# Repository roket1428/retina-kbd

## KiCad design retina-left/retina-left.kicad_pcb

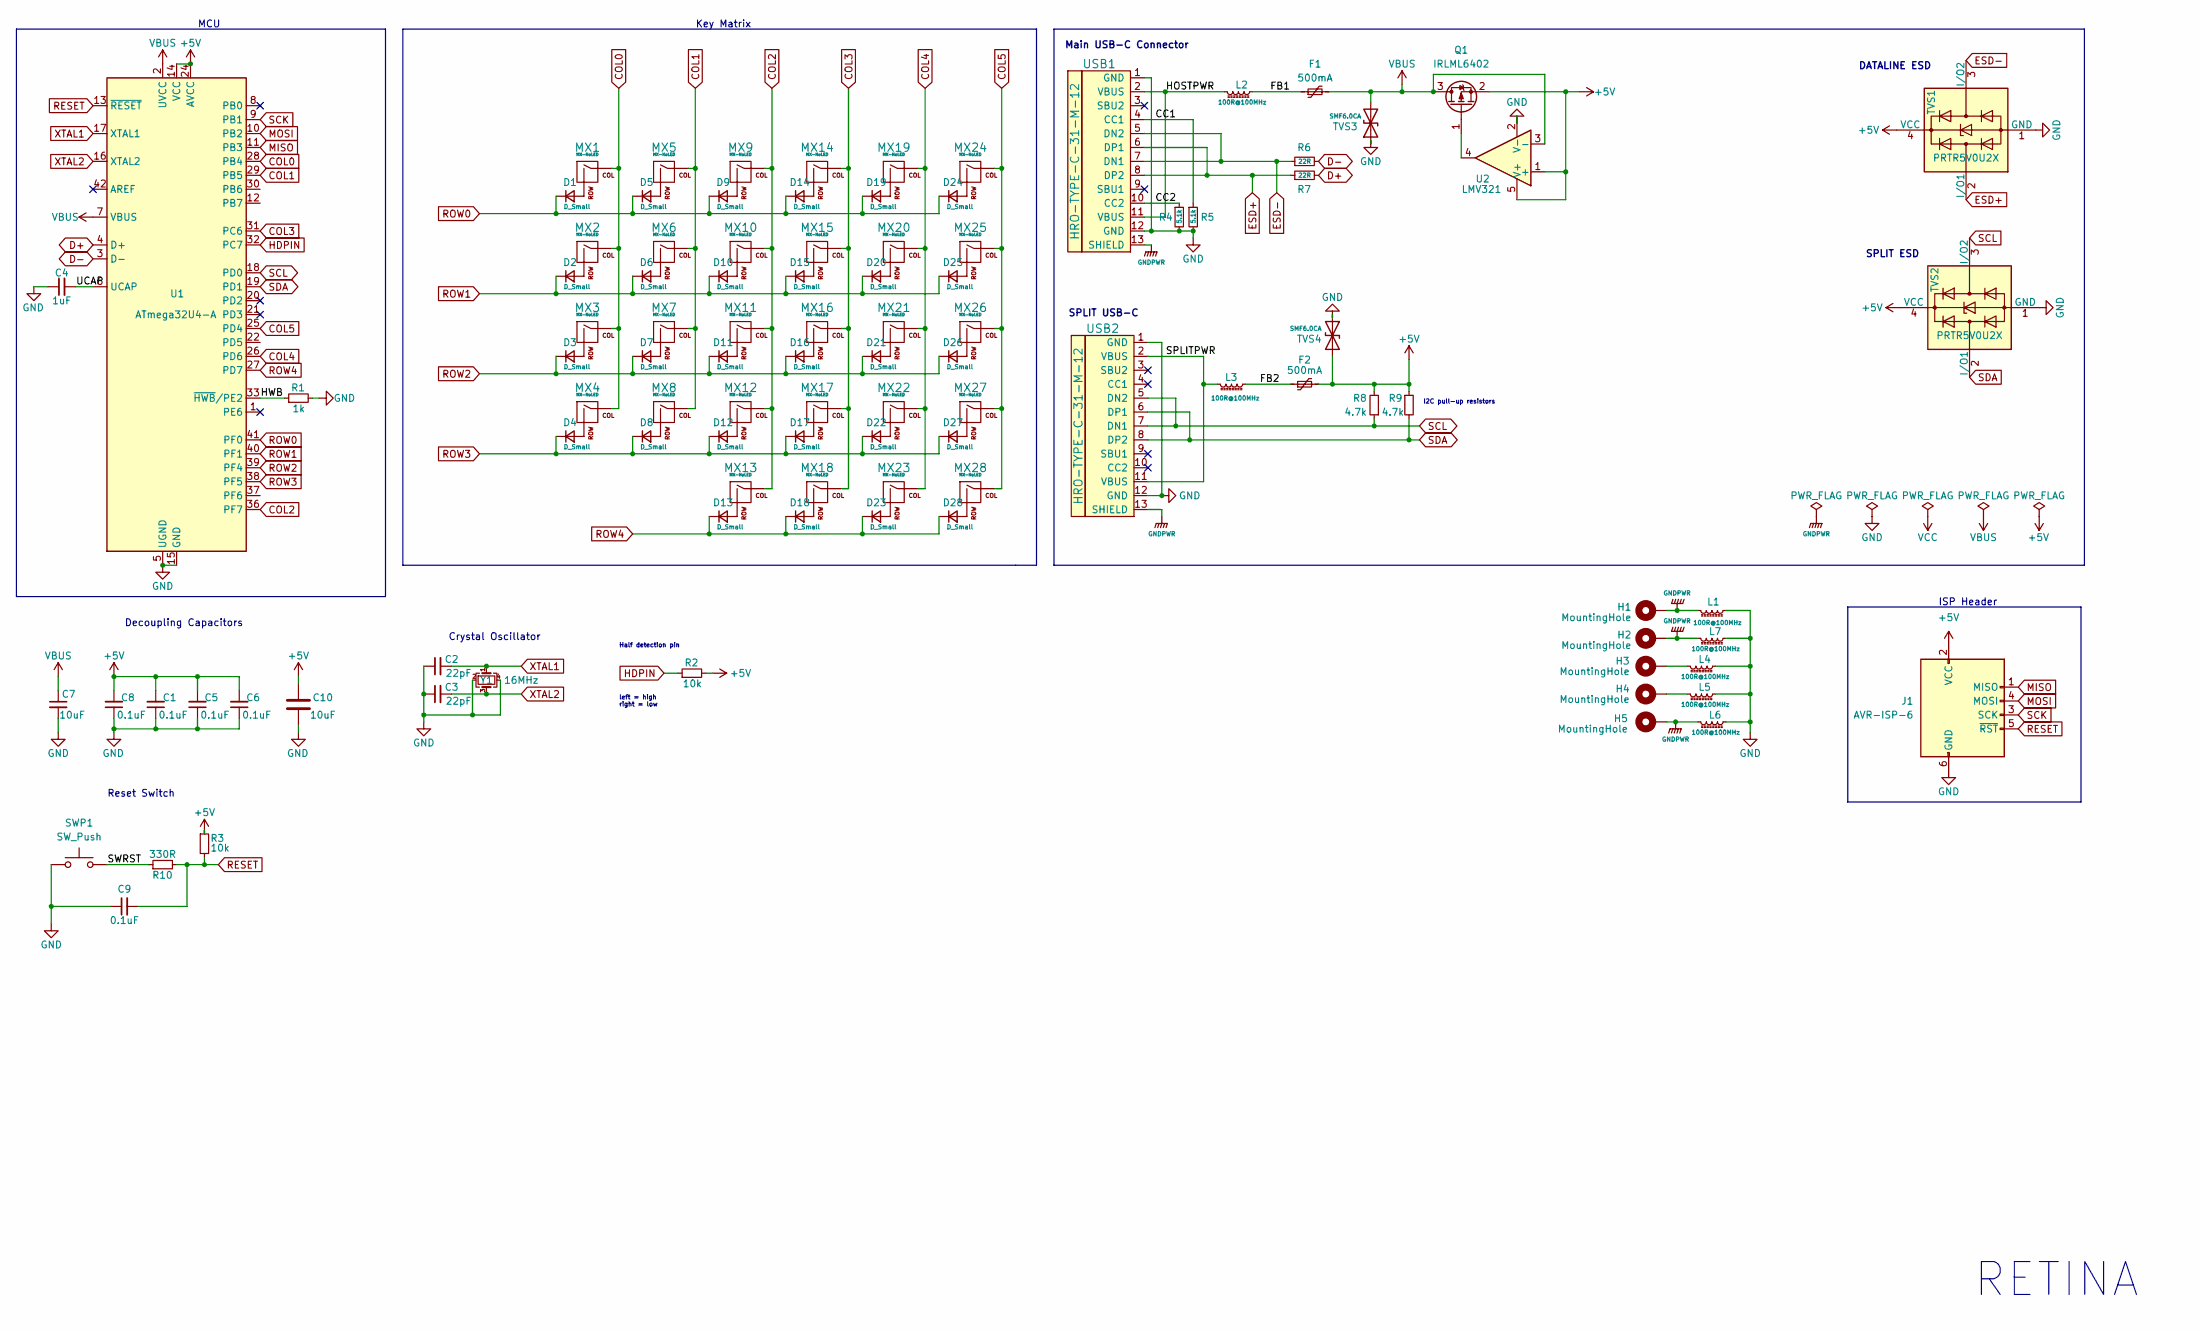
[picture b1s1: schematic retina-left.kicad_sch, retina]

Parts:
C1, C5, C6, C8, C9: 0.1uF; C_0805_2012Metric_Pad1.18x1.45mm_HandSolder
C2, C3: 22pF; C_0805_2012Metric_Pad1.18x1.45mm_HandSolder
C4: 1uF; C_0805_2012Metric_Pad1.18x1.45mm_HandSolder
C7, C10: 10uF; C_0805_2012Metric_Pad1.18x1.45mm_HandSolder
D1, D2, D3, D4, D5, D6, D7, D8, D9, D10, D11, D12, D13, D14, D15, D16, D17, D18, D19, D20, D21, D22, D23, D24, D25, D26, D27, D28: D_Small; D_DO-35_SOD27_P7.62mm
F1, F2: 500mA; Fuse_1206_3216Metric_Pad1.42x1.75mm_HandSolder
H1, H2, H3, H4, H5: MountingHole; MountingHole_2.2mm_M2_Pad_Via
J1: AVR-ISP-6; Conn_AVR_ISP_6
L1, L2, L3, L4, L5, L6, L7: 100R@100MHz; L_0805_2012Metric_Pad1.05x1.20mm_HandSolder
MX1, MX2, MX3, MX4, MX5, MX6, MX7, MX8, MX9, MX10, MX11, MX12, MX13, MX14, MX15, MX16, MX17, MX18, MX19, MX20, MX21, MX22, MX23, MX24, MX25, MX26, MX27, MX28: MX-NoLED; MXOnly-1U-Hotswap
Q1: IRLML6402; SOT-23_Handsoldering
R1: 1k; R_0805_2012Metric_Pad1.20x1.40mm_HandSolder
R2, R3: 10k; R_0805_2012Metric_Pad1.20x1.40mm_HandSolder
R4, R5: 5.1k; R_0805_2012Metric_Pad1.20x1.40mm_HandSolder
R6, R7: 22R; R_0805_2012Metric_Pad1.20x1.40mm_HandSolder
R8, R9: 4.7k; R_0805_2012Metric_Pad1.20x1.40mm_HandSolder
R10: 330R; R_0805_2012Metric_Pad1.20x1.40mm_HandSolder
SWP1: SW_Push; K2-1187SQ-A4SW-06
TVS1, TVS2: PRTR5V0U2X; SOT-143
TVS3, TVS4: SMF6.0CA; D_SOD-123F
U1: ATmega32U4-A; TQFP-44_10x10mm_P0.8mm
U2: LMV321; SOT-23-5_HandSoldering
USB1, USB2: HRO-TYPE-C-31-M-12; HRO-TYPE-C-31-M-12-HandSoldering
Y1: 16MHz; Crystal_SMD_3225-4Pin_3.2x2.5mm_HandSoldering

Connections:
+5V: C1.2, C5.2, C6.2, C8.2, C10.2, F2.2, J1.2 (VCC), Q1.2 (S), R2.2, R3.1, R8.2, R9.1, TVS1.4 (VCC), TVS2.4 (VCC), TVS4.2 (A2), U1.14 (VCC), U1.24 (AVCC), U1.34 (VCC), U1.44 (AVCC), U2.1 (+), U2.5 (V+)
/CC1: R5.1, USB1.4 (CC1)
/CC2: R4.1, USB1.10 (CC2)
/FB1: F1.1, L2.1
/FB2: F2.1, L3.1
/HOSTPWR: L2.2, USB1.2 (VBUS), USB1.11 (VBUS)
/HWB: R1.1, U1.33 (~HWB/PE2)
/SPLITPWR: L3.2, USB2.2 (VBUS), USB2.11 (VBUS)
/SWRST: R10.1, SWP1.2
/UCAP: C4.2, U1.6 (UCAP)
COL0: MX1.1 (COL), MX2.1 (COL), MX3.1 (COL), MX4.1 (COL), U1.28 (PB4)
COL1: MX5.1 (COL), MX6.1 (COL), MX7.1 (COL), MX8.1 (COL), U1.29 (PB5)
COL2: MX9.1 (COL), MX10.1 (COL), MX11.1 (COL), MX12.1 (COL), MX13.1 (COL), U1.36 (PF7)
COL3: MX14.1 (COL), MX15.1 (COL), MX16.1 (COL), MX17.1 (COL), MX18.1 (COL), U1.31 (PC6)
COL4: MX19.1 (COL), MX20.1 (COL), MX21.1 (COL), MX22.1 (COL), MX23.1 (COL), U1.26 (PD6)
COL5: MX24.1 (COL), MX25.1 (COL), MX26.1 (COL), MX27.1 (COL), MX28.1 (COL), U1.25 (PD4)
D+: R7.2, U1.4 (D+)
D-: R6.2, U1.3 (D-)
ESD+: R7.1, TVS1.2 (I/O1), USB1.6 (DP1), USB1.8 (DP2)
ESD-: R6.1, TVS1.3 (I/O2), USB1.5 (DN2), USB1.7 (DN1)
GND: C1.1, C2.1, C3.1, C4.1, C5.1, C6.1, C7.2, C8.1, C9.1, C10.1, J1.6 (GND), L1.1, L4.1, L5.1, L6.1, L7.1, R1.2, R4.2, R5.2, SWP1.1, TVS1.1 (GND), TVS2.1 (GND), TVS3.1 (A1), TVS4.1 (A1), U1.5 (UGND), U1.15 (GND), U1.23 (GND), U1.35 (GND), U1.43 (GND), U2.2 (V-), USB1.1 (GND), USB1.12 (GND), USB2.1 (GND), USB2.12 (GND), Y1.2, Y1.4
GNDPWR: H1.1, H2.1, H5.1, L1.2, L6.2, L7.2, USB1.13 (SHIELD), USB2.13 (SHIELD)
HDPIN: R2.1, U1.32 (PC7)
MISO: J1.1 (MISO), U1.11 (PB3)
MOSI: J1.4 (MOSI), U1.10 (PB2)
unnamed: D1.2 (A), MX1.2 (ROW)
unnamed: D2.2 (A), MX2.2 (ROW)
unnamed: D3.2 (A), MX3.2 (ROW)
unnamed: D4.2 (A), MX4.2 (ROW)
unnamed: D5.2 (A), MX5.2 (ROW)
unnamed: D6.2 (A), MX6.2 (ROW)
unnamed: D7.2 (A), MX7.2 (ROW)
unnamed: D8.2 (A), MX8.2 (ROW)
unnamed: D9.2 (A), MX9.2 (ROW)
unnamed: D10.2 (A), MX10.2 (ROW)
unnamed: D11.2 (A), MX11.2 (ROW)
unnamed: D12.2 (A), MX12.2 (ROW)
unnamed: D13.2 (A), MX13.2 (ROW)
unnamed: D14.2 (A), MX14.2 (ROW)
unnamed: D15.2 (A), MX15.2 (ROW)
unnamed: D16.2 (A), MX16.2 (ROW)
unnamed: D17.2 (A), MX17.2 (ROW)
unnamed: D18.2 (A), MX18.2 (ROW)
unnamed: D19.2 (A), MX19.2 (ROW)
unnamed: D20.2 (A), MX20.2 (ROW)
unnamed: D21.2 (A), MX21.2 (ROW)
unnamed: D22.2 (A), MX22.2 (ROW)
unnamed: D23.2 (A), MX23.2 (ROW)
unnamed: D24.2 (A), MX24.2 (ROW)
unnamed: D25.2 (A), MX25.2 (ROW)
unnamed: D26.2 (A), MX26.2 (ROW)
unnamed: D27.2 (A), MX27.2 (ROW)
unnamed: D28.2 (A), MX28.2 (ROW)
unnamed: H3.1, L4.2
unnamed: H4.1, L5.2
unnamed: Q1.1 (G), U2.4
RESET: C9.2, J1.5 (~RST), R3.2, R10.2, U1.13 (~RESET)
ROW0: D1.1 (K), D5.1 (K), D9.1 (K), D14.1 (K), D19.1 (K), D24.1 (K), U1.41 (PF0)
ROW1: D2.1 (K), D6.1 (K), D10.1 (K), D15.1 (K), D20.1 (K), D25.1 (K), U1.40 (PF1)
ROW2: D3.1 (K), D7.1 (K), D11.1 (K), D16.1 (K), D21.1 (K), D26.1 (K), U1.39 (PF4)
ROW3: D4.1 (K), D8.1 (K), D12.1 (K), D17.1 (K), D22.1 (K), D27.1 (K), U1.38 (PF5)
ROW4: D13.1 (K), D18.1 (K), D23.1 (K), D28.1 (K), U1.27 (PD7)
SCK: J1.3 (SCK), U1.9 (PB1)
SCL: R8.1, TVS2.3 (I/O2), U1.18 (PD0), USB2.5 (DN2), USB2.7 (DN1)
SDA: R9.2, TVS2.2 (I/O1), U1.19 (PD1), USB2.6 (DP1), USB2.8 (DP2)
VBUS: C7.1, F1.2, Q1.3 (D), TVS3.2 (A2), U1.2 (UVCC), U1.7 (VBUS), U2.3 (-)
XTAL1: C2.2, U1.17 (XTAL1), Y1.1
XTAL2: C3.2, U1.16 (XTAL2), Y1.3

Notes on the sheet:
Reset Switch
MCU
SPLIT ESD
DATALINE ESD
Crystal Oscillator
I2C pull-up resistors
left = high right = low
Half detection pin
Main USB-C Connector
SPLIT USB-C
Decoupling Capacitors
ISP Header
Key Matrix
RETINA

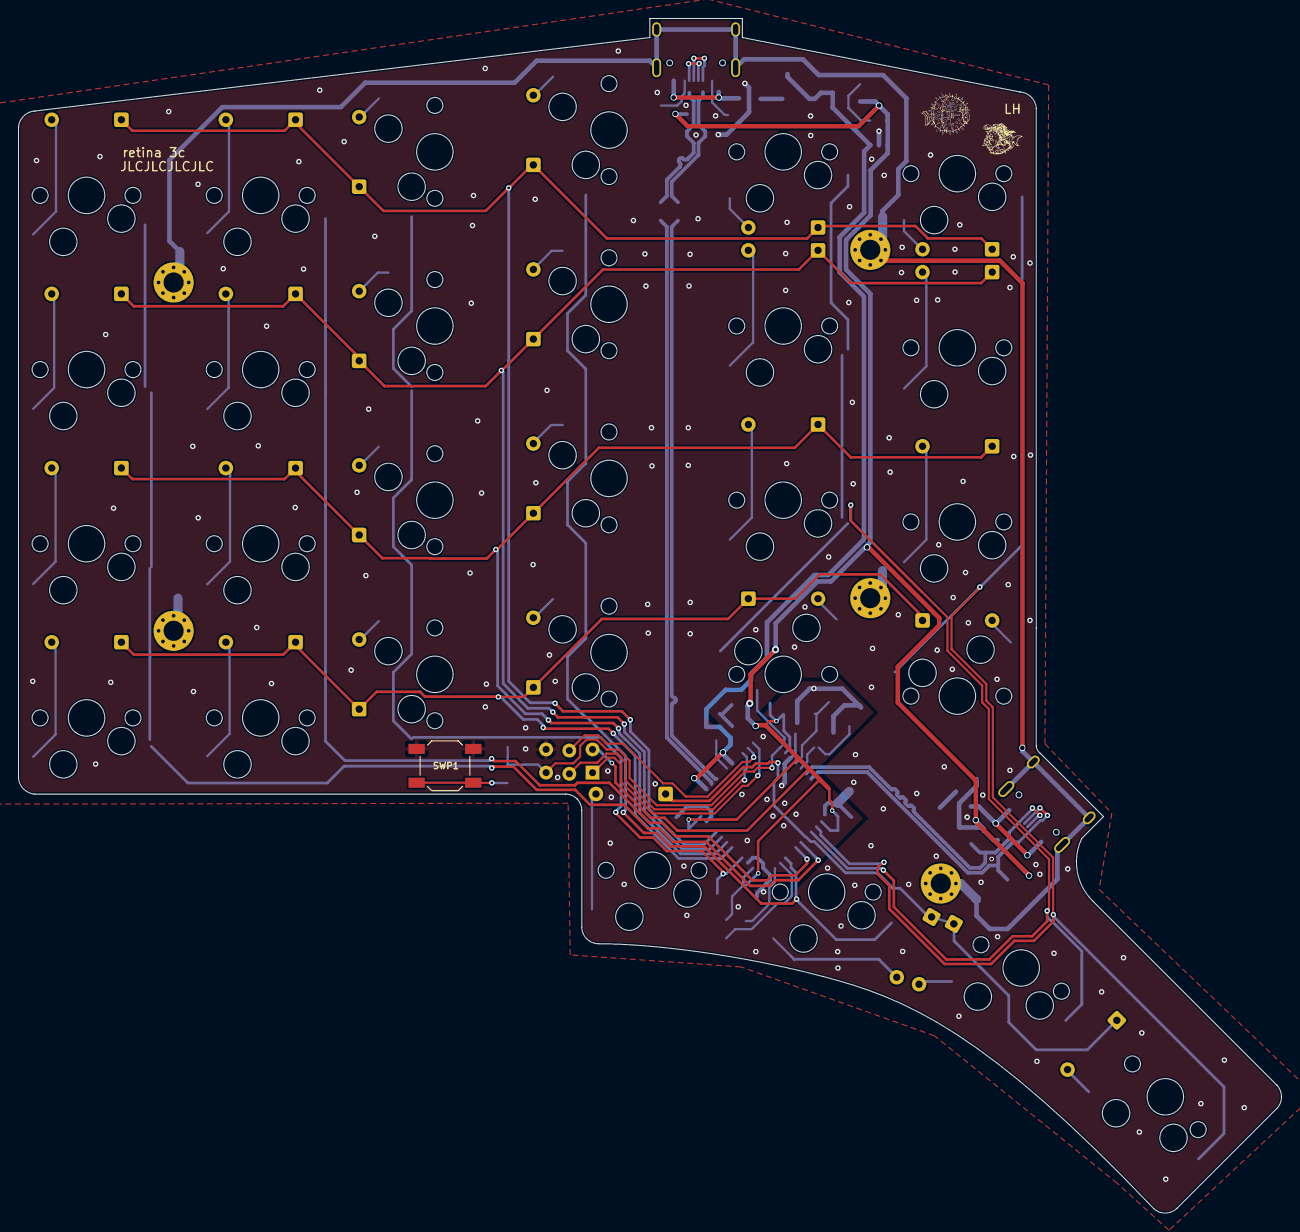
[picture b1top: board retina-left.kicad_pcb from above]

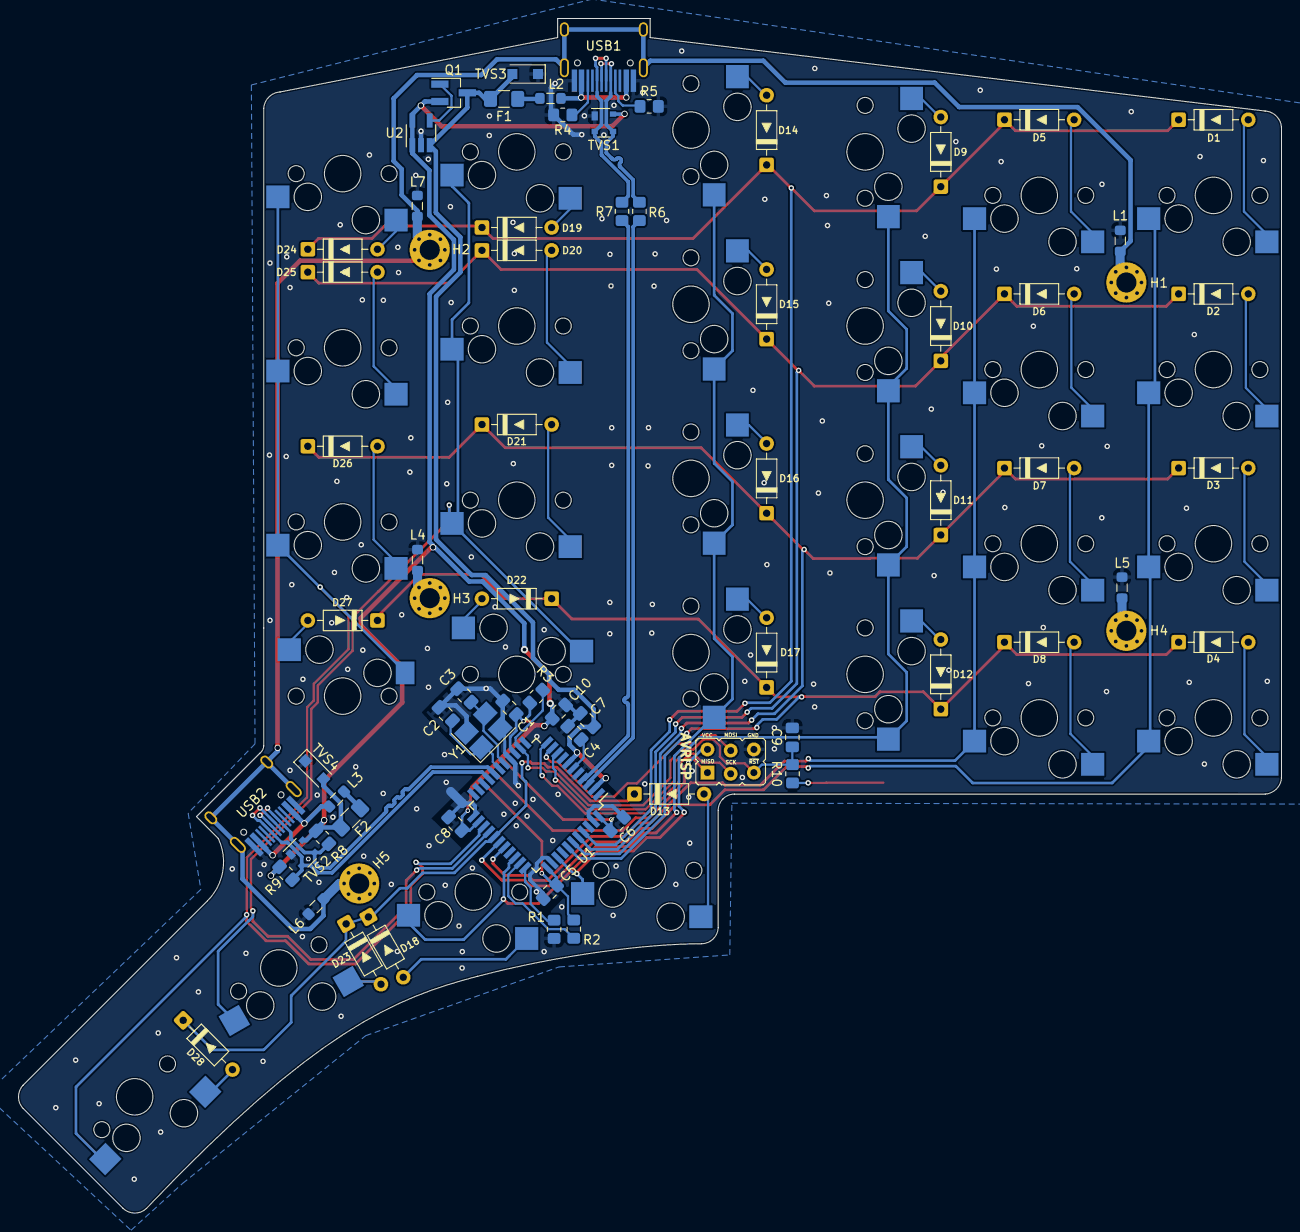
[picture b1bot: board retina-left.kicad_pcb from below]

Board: 2 copper layers, 138.1 x 130.7 mm, 102 parts (73 on the bottom side), 68 nets.

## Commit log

2023-08-20 initial github import
